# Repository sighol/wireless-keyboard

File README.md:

# Sighol-44

# Installation

Remember to add the [marbastlib](https://github.com/ebastler/marbastlib) symbol and footprints library.
Check the github page for installation instructions.

# Documentation

[Nice nano pinout and schematic](https://nicekeyboards.com/docs/nice-nano/pinout-schematic)

## [Video about batteries](https://www.youtube.com/watch?v=zoCKINGh2DQ)

- GEt mill max sockets that are avtagbare.
- Get taller ones so that battery fit underneath.
- Solder on the power switch early on. He said "the first thing", but I am not sure if
  that matters a lot.

## Nice View

https://nicekeyboards.com/docs/nice-view/pinout-schematic#default-pins

- CS: D1/P0.06
- SCL: D2/P0.17
- MOSI: D3/P0.20

# Parts

- 2 x [Nice!Nano V2](https://42keebs.eu/shop/parts/controllers/nice-nano-v2-wireless-controller/)
- 2 x [Controller sockets/pins/headers medium](https://42keebs.eu/shop/parts/components/controller-sockets-pins-mill-max-generic/?attribute_pack=Medium+Profile+Sockets+%2B+Pins+%2825%29). Medium will fit 3mm batteries.
- 1 x [Nice!view](https://42keebs.eu/shop/parts/niceview-power-efficient-lcd-display/). I only need one for the left half.
- 2 x [SDM power switch](https://42keebs.eu/shop/parts/components/power-switch/?attribute_type=Micro+SMD+SPDT).
- 2 x [reset switch](https://42keebs.eu/shop/parts/components/reset-switch/).
- [Batteries](https://www.aliexpress.com/item/1005007625961666.html?spm=a2g0o.productlist.main.59.9ca11d420CydvJ&algo_pvid=120edaba-9165-4a9c-8ff5-5bade77d414c&algo_exp_id=120edaba-9165-4a9c-8ff5-5bade77d414c-29&pdp_ext_f=%7B%22order%22%3A%223%22%2C%22eval%22%3A%221%22%7D&pdp_npi=4%40dis%21NOK%2189.36%2178.63%21%21%2156.90%2150.07%21%40211b628117393867808432677e90e9%2112000041552681850%21sea%21NO%210%21ABX&curPageLogUid=lpMMqd58MoUq&utparam-url=scene%3Asearch%7Cquery_from%3A#nav-specification)

Total: 93.95 EUR on 42keebs.eu.

# TODO:

- Look for batteries and find one that fits.
- Check that the footprint for the RESET switch matches keeb42

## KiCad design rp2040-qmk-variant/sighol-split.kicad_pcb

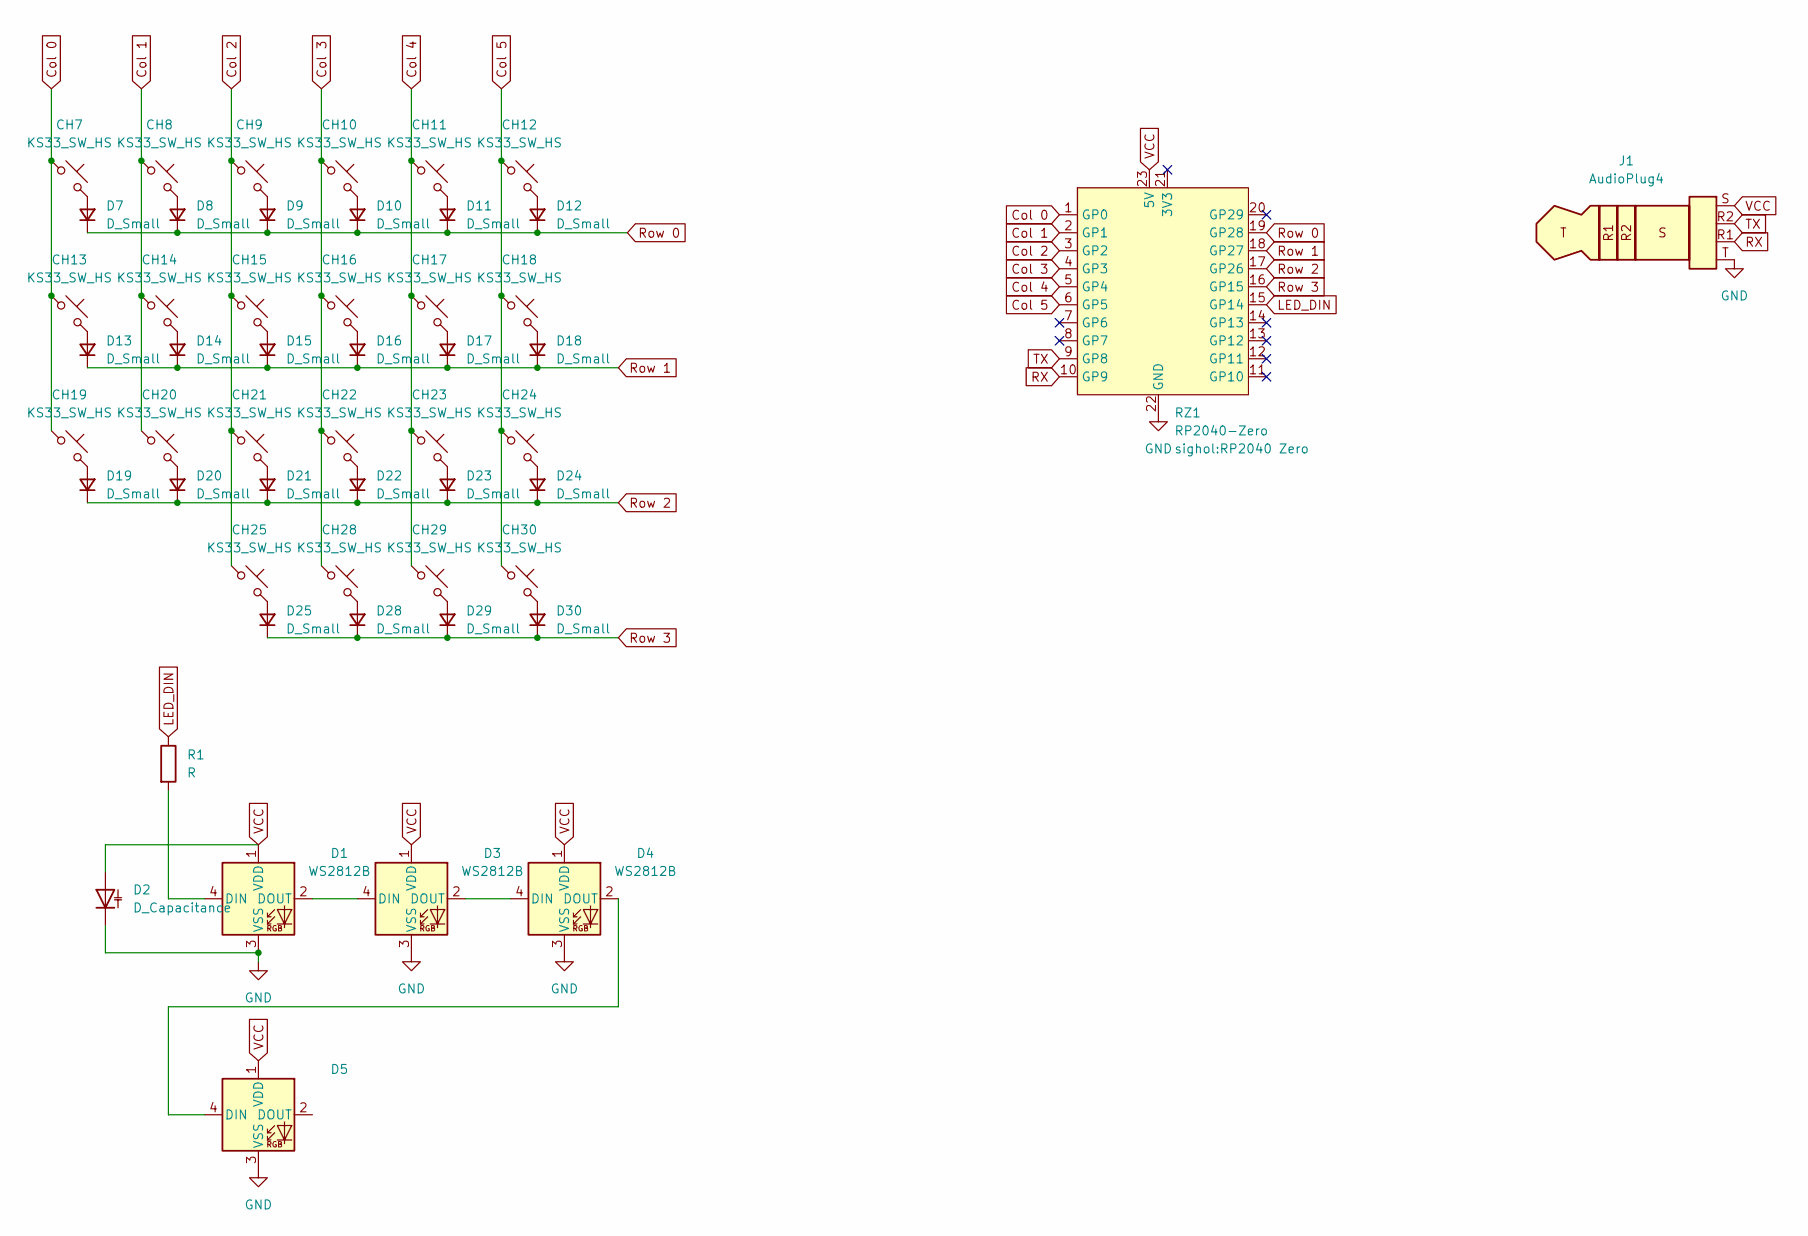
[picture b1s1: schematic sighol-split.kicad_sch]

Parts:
CH7, CH8, CH9, CH10, CH11, CH12, CH13, CH14, CH15, CH16, CH17, CH18, CH19, CH20, CH21, CH22, CH23, CH24, CH25, CH28, CH29, CH30: KS33_SW_HS; Kailh_socket_PG1350 reversible HS-only
D1, D3, D4, D5: WS2812B; LED_WS2812B_PLCC4_5.0x5.0mm_P3.2mm_reversible
D2: D_Capacitance; CP_Radial_D5.0mm_P2.00mm
D7, D8, D9, D10, D11, D12, D13, D14, D15, D16, D17, D18, D19, D20, D21, D22, D23, D24, D25, D28, D29, D30: D_Small; SOD-123 reversible
J1: AudioPlug4; TRRS-PJ-320A
R1: R; R_Axial_DIN0207_L6.3mm_D2.5mm_P2.54mm_Vertical
RZ1: RP2040-Zero; RP2040 Zero

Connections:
Col 0: CH7.1, CH13.1, CH19.1, RZ1.1 (GP0)
Col 1: CH8.1, CH14.1, CH20.1, RZ1.2 (GP1)
Col 2: CH9.1, CH15.1, CH21.1, CH25.1, RZ1.3 (GP2)
Col 3: CH10.1, CH16.1, CH22.1, CH28.1, RZ1.4 (GP3)
Col 4: CH11.1, CH17.1, CH23.1, CH29.1, RZ1.5 (GP4)
Col 5: CH12.1, CH18.1, CH24.1, CH30.1, RZ1.6 (GP5)
GND: D1.3 (VSS), D2.1 (K), D3.3 (VSS), D4.3 (VSS), D5.3 (VSS), J1.T, RZ1.22 (GND)
LED_DIN: R1.1, RZ1.15 (GP14)
unnamed: D1.4 (DIN), R1.2
unnamed: D1.2 (DOUT), D3.4 (DIN)
unnamed: D3.2 (DOUT), D4.4 (DIN)
unnamed: D4.2 (DOUT), D5.4 (DIN)
unnamed: CH7.2, D7.2 (A)
unnamed: CH8.2, D8.2 (A)
unnamed: CH9.2, D9.2 (A)
unnamed: CH10.2, D10.2 (A)
unnamed: CH11.2, D11.2 (A)
unnamed: CH12.2, D12.2 (A)
unnamed: CH13.2, D13.2 (A)
unnamed: CH14.2, D14.2 (A)
unnamed: CH15.2, D15.2 (A)
unnamed: CH16.2, D16.2 (A)
unnamed: CH17.2, D17.2 (A)
unnamed: CH18.2, D18.2 (A)
unnamed: CH19.2, D19.2 (A)
unnamed: CH20.2, D20.2 (A)
unnamed: CH21.2, D21.2 (A)
unnamed: CH22.2, D22.2 (A)
unnamed: CH23.2, D23.2 (A)
unnamed: CH24.2, D24.2 (A)
unnamed: CH25.2, D25.2 (A)
unnamed: CH28.2, D28.2 (A)
unnamed: CH29.2, D29.2 (A)
unnamed: CH30.2, D30.2 (A)
RX: J1.R1, RZ1.10 (GP9)
Row 0: D7.1 (K), D8.1 (K), D9.1 (K), D10.1 (K), D11.1 (K), D12.1 (K), RZ1.19 (GP28)
Row 1: D13.1 (K), D14.1 (K), D15.1 (K), D16.1 (K), D17.1 (K), D18.1 (K), RZ1.18 (GP27)
Row 2: D19.1 (K), D20.1 (K), D21.1 (K), D22.1 (K), D23.1 (K), D24.1 (K), RZ1.17 (GP26)
Row 3: D25.1 (K), D28.1 (K), D29.1 (K), D30.1 (K), RZ1.16 (GP15)
TX: J1.R2, RZ1.9 (GP8)
VCC: D1.1 (VDD), D2.2 (A), D3.1 (VDD), D4.1 (VDD), D5.1 (VDD), J1.S, RZ1.23 (5V)

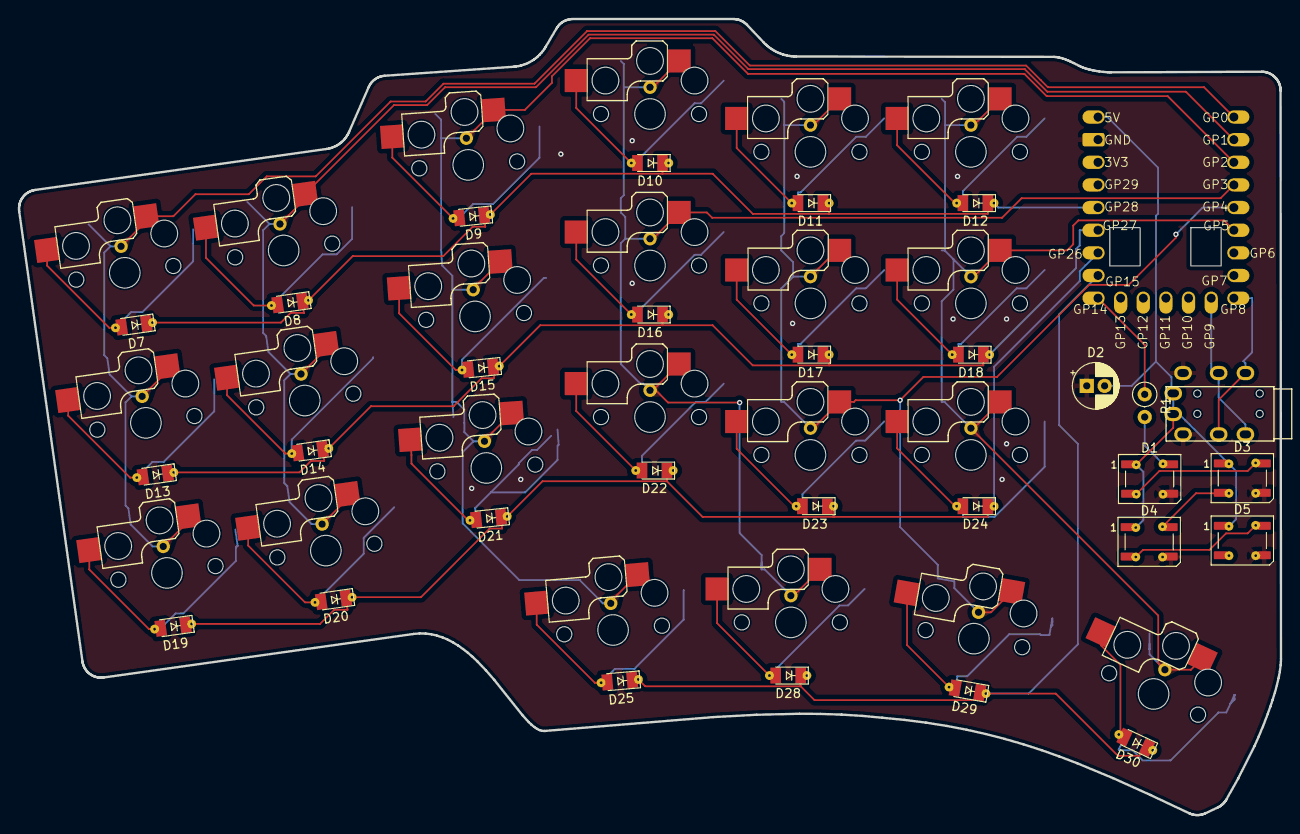
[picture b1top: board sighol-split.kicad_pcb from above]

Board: 2 copper layers, 141.6 x 89.3 mm, 52 parts (1 on the bottom side), 41 nets.

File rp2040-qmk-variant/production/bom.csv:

Designator,Footprint,Quantity,Value,LCSC Part #
"CH10, CH11, CH12, CH13, CH14, CH15, CH16, CH17, CH18, CH19, CH20, CH21, CH22, CH23, CH24, CH25, CH28, CH29, CH30, CH7, CH8, CH9",Kailh_socket_PG1350 reversible HS-only,22,KS33_SW_HS,
"D1, D3, D4, D5",LED_WS2812B_PLCC4_5.0x5.0mm_P3.2mm_reversible,4,WS2812B,
"D10, D11, D12, D13, D14, D15, D16, D17, D18, D19, D20, D21, D22, D23, D24, D25, D28, D29, D30, D7, D8, D9",SOD-123 reversible,22,D_Small,
D2,CP_Radial_D5.0mm_P2.00mm,1,D_Capacitance,
J1,TRRS-PJ-320A,1,AudioPlug4,
R1,R_Axial_DIN0207_L6.3mm_D2.5mm_P2.54mm_Vertical,1,R,
RZ1,RP2040 Zero,1,RP2040-Zero,

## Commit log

2024-03-19 Created almost all routes: non-reversible left side
2024-03-19 connected all routes
2024-03-19 New edge cut
2024-03-21 new footprint
2024-03-21 more work
2024-03-21 More routing
2024-03-21 Full wiring
2024-03-22 moved right index row and fix teardrops
2024-03-22 More stuff
2024-03-22 edge cut
2024-03-22 Prettier edge cut
2024-03-23 Nothing
2024-09-21 Starting on new wireless build
2024-09-21 Move to sighol.kicad_sym
2024-09-21 README.md
2024-09-21 blueprint.png in readme
2024-09-21 test
2024-09-21 blueprint
2024-09-21 remove blueprint again
2024-09-21 edge-cut and blueprint
2024-09-21 keyboard.png
2025-02-09 work
2025-02-10 remove nice-view-kicad submodule and remove display 2
2025-02-11 docs and more tracing and nice view
2025-02-11 README
2025-02-12 No longer need to have screen protector.
    > https://discord.com/channels/675924128108118016/991852441832259714/1339304749198999686
2025-02-12 Create reversible SW_MSK12CO2-HB, and connect all traces
2025-02-13 Move RST and PW, but leave disconnected
2025-02-13 Smoother edge cut + moved mcu further down for more margin
2025-02-13 Connect all traces again
2025-02-13 Slightly smoother edge cut
2025-02-13 copper layer fill zone
2025-02-13 update todo
2025-02-13 README tood
2025-02-15 nothin much
2025-02-16 Ground fill and connect nicenano to 3V3 instead of Bat+
2025-02-18 Update docs image
2025-02-21 Fix RESET switch
2025-02-21 fabrication n all
2025-02-21 sighol44
2025-03-11 Fix RP2040 build
2025-03-11 rp2040: no-connect
2025-03-11 Make footprint for diode nicer
2025-03-11 More footprint silkscreens
2025-03-16 SMD diodes + holes for the boot and reset pins
2025-03-16 Added LEDs that I think are meant to be used for indoor lightning
2025-03-16 fixup! SMD diodes + holes for the boot and reset pins
2025-03-16 To production, again
2025-04-15 Stuff
2025-04-15 Add rp2040-qmk-variant
